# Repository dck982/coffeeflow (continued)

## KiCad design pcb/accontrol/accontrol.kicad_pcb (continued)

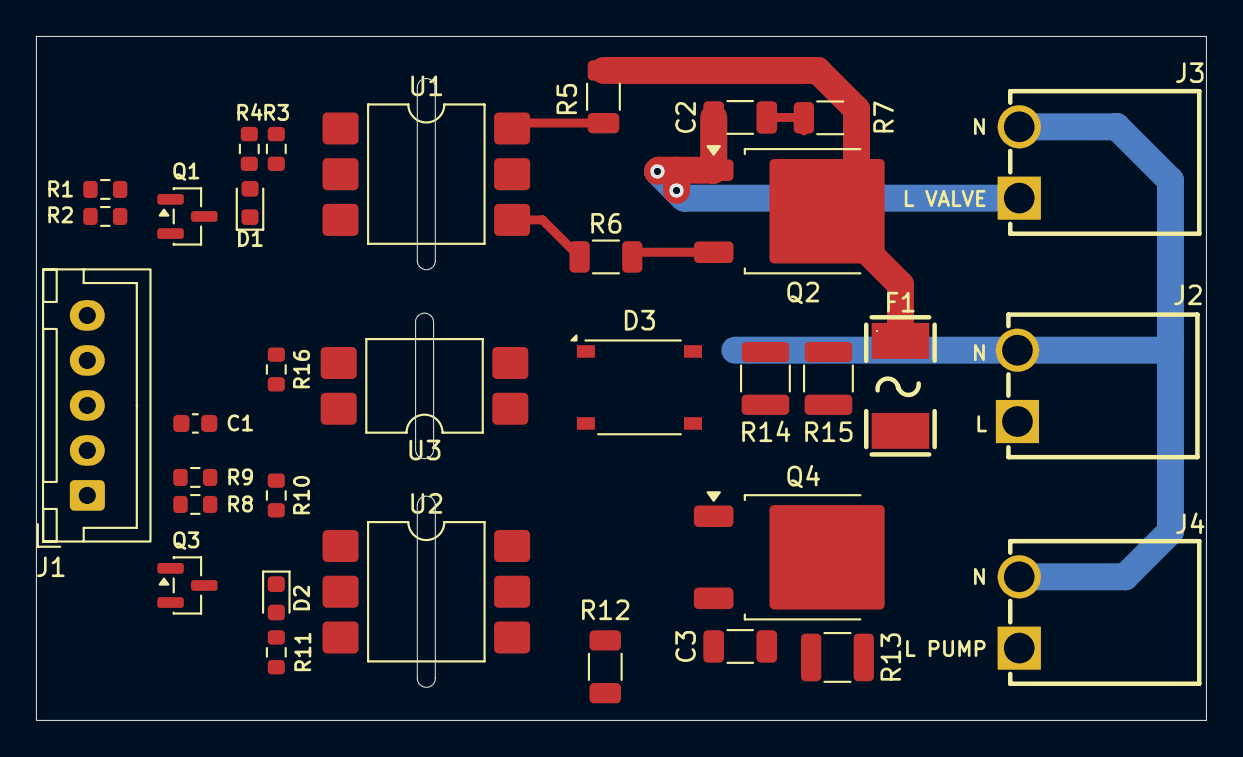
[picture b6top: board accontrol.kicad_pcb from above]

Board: 2 copper layers, 65.0 x 38.0 mm, 34 parts (0 on the bottom side), 29 nets.

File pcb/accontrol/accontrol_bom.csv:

"Reference","Value","Footprint","DNP","MPN","LCSC","Note"
"C1","1uF","Capacitor_SMD:C_0603_1608Metric","","","","3V3 decoupling at J1"
"C2","10nF 1kV","Capacitor_SMD:C_1206_3216Metric","","","","Snubber, X7R 1000 V"
"C3","10nF 1kV","Capacitor_SMD:C_1206_3216Metric","","","","Snubber, X7R 1000 V"
"D1","RED","LED_SMD:LED_0603_1608Metric","","","","Channel indicator"
"D2","RED","LED_SMD:LED_0603_1608Metric","","","","Channel indicator"
"D3","ABS6","Diode_SMD:Diode_Bridge_Diotec_ABS","","ABS6","C48642435","Hongjiacheng ABS6, 600 V, ABS package (4 mm pitch)"
"F1","2A 250V fast","Accontrol_Local:F2410","","MF2410F2.000TM","C83797","AEM 2410 fast, 100 A breaking at 250 VAC"
"J1","CTRL","Connector_JST:JST_XH_B5B-XH-A_1x05_P2.50mm_Vertical","","B5B-XH-A(LF)(SN)","","1 GND, 2 3V3, 3 DIM, 4 ZC, 5 SSR"
"J2","MAINS_IN","Accontrol_Local:CONN-TH_P3.96_HT396R-3.96-2P","","HT396R-3.96-2P","C577799","1 L, 2 N"
"J3","VALVE","Accontrol_Local:CONN-TH_P3.96_HT396R-3.96-2P","","HT396R-3.96-2P","C577799","1 L (switched), 2 N"
"J4","PUMP","Accontrol_Local:CONN-TH_P3.96_HT396R-3.96-2P","","HT396R-3.96-2P","C577799","1 L (switched), 2 N"
"Q1","SS8050","Package_TO_SOT_SMD:SOT-23","","SS8050 (Y1)","","SOT-23 pinout 1 B, 2 E, 3 C"
"Q2","BT136S","Package_TO_SOT_SMD:TO-252-2","","BT136S","C23427","DPAK: 1 MT1, 2 MT2 (tab), 3 G"
"Q3","SS8050","Package_TO_SOT_SMD:SOT-23","","SS8050 (Y1)","","SOT-23 pinout 1 B, 2 E, 3 C"
"Q4","BT136S","Package_TO_SOT_SMD:TO-252-2","","BT136S","C23427","DPAK: 1 MT1, 2 MT2 (tab), 3 G"
"R1","1k","Resistor_SMD:R_0603_1608Metric","","","","Base resistor"
"R2","4.7k","Resistor_SMD:R_0603_1608Metric","","","","Holds the channel off when the cable is unplugged"
"R3","180","Resistor_SMD:R_0603_1608Metric","","","","MOC LED: (3.3-1.2-0.1)/180 = 11 mA typ, >= 8 mA worst case"
"R4","1k","Resistor_SMD:R_0603_1608Metric","","","","Indicator LED ~1.2 mA"
"R5","360","Resistor_SMD:R_1206_3216Metric","","","","MT2 series resistor (M5Stack design)"
"R6","330","Resistor_SMD:R_1206_3216Metric","","","","Gate series resistor (M5Stack design)"
"R7","39","Resistor_SMD:R_1206_3216Metric","","","","Snubber"
"R8","1k","Resistor_SMD:R_0603_1608Metric","","","","Base resistor"
"R9","4.7k","Resistor_SMD:R_0603_1608Metric","","","","Holds the channel off when the cable is unplugged"
"R10","180","Resistor_SMD:R_0603_1608Metric","","","","MOC LED: (3.3-1.2-0.1)/180 = 11 mA typ, >= 8 mA worst case"
"R11","1k","Resistor_SMD:R_0603_1608Metric","","","","Indicator LED ~1.2 mA"
"R12","1k","Resistor_SMD:R_1206_3216Metric","","","","MT2 series resistor, gate driven directly (RobotDyn design)"
"R13","39","Resistor_SMD:R_1210_3225Metric","","RC1210JR-0739RL","C728404","Snubber, 1210 for the C3 discharge at each firing"
"R14","120k","Resistor_SMD:R_1210_3225Metric","","1210W2F1203T5E","C422421","ZC sense, 2 x 120k 1210 in series = 240k: 0.11 W (22 %) and 160 V peak each"
"R15","120k","Resistor_SMD:R_1210_3225Metric","","1210W2F1203T5E","C422421","ZC sense, see R14"
"R16","10k","Resistor_SMD:R_0603_1608Metric","","","","ZC pull-up (RobotDyn value)"
"U1","MOC3043M","Accontrol_Local:SMDIP-6_W9.53mm_Slot","","MOC3043M","","IFT max 5 mA; ~11 mA with 180R at 3.3 V"
"U2","MOC3023M","Accontrol_Local:SMDIP-6_W9.53mm_Slot","","MOC3023M","","IFT max 5 mA; ~11 mA with 180R at 3.3 V"
"U3","EL817C","Accontrol_Local:SMDIP-4_W9.53mm_Slot","","EL817S1(C)(TU)-F","","CTR rank C 200-400 %"
